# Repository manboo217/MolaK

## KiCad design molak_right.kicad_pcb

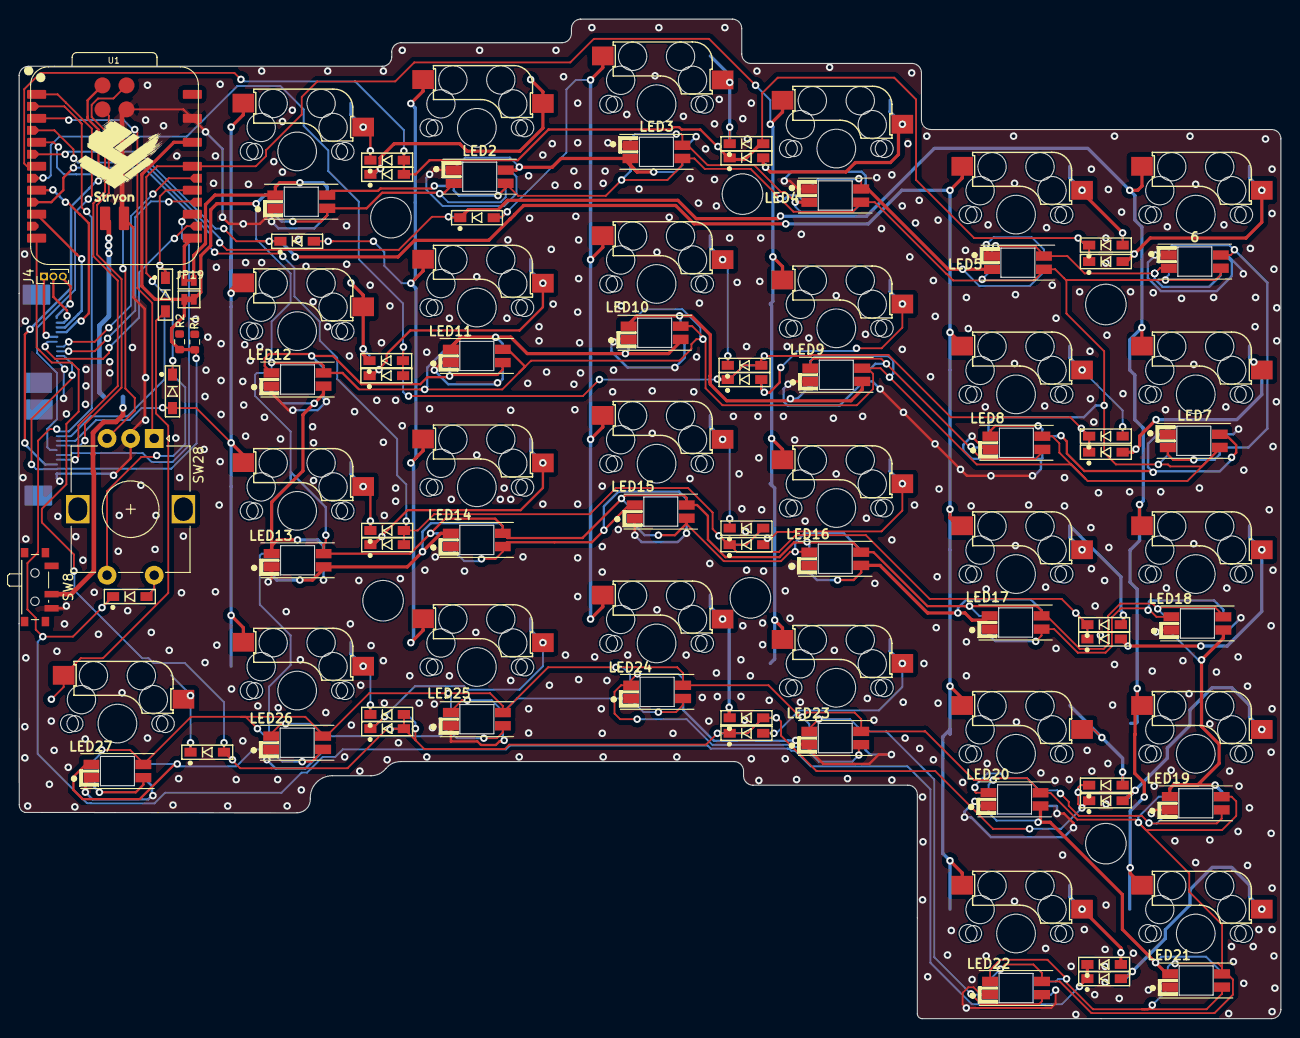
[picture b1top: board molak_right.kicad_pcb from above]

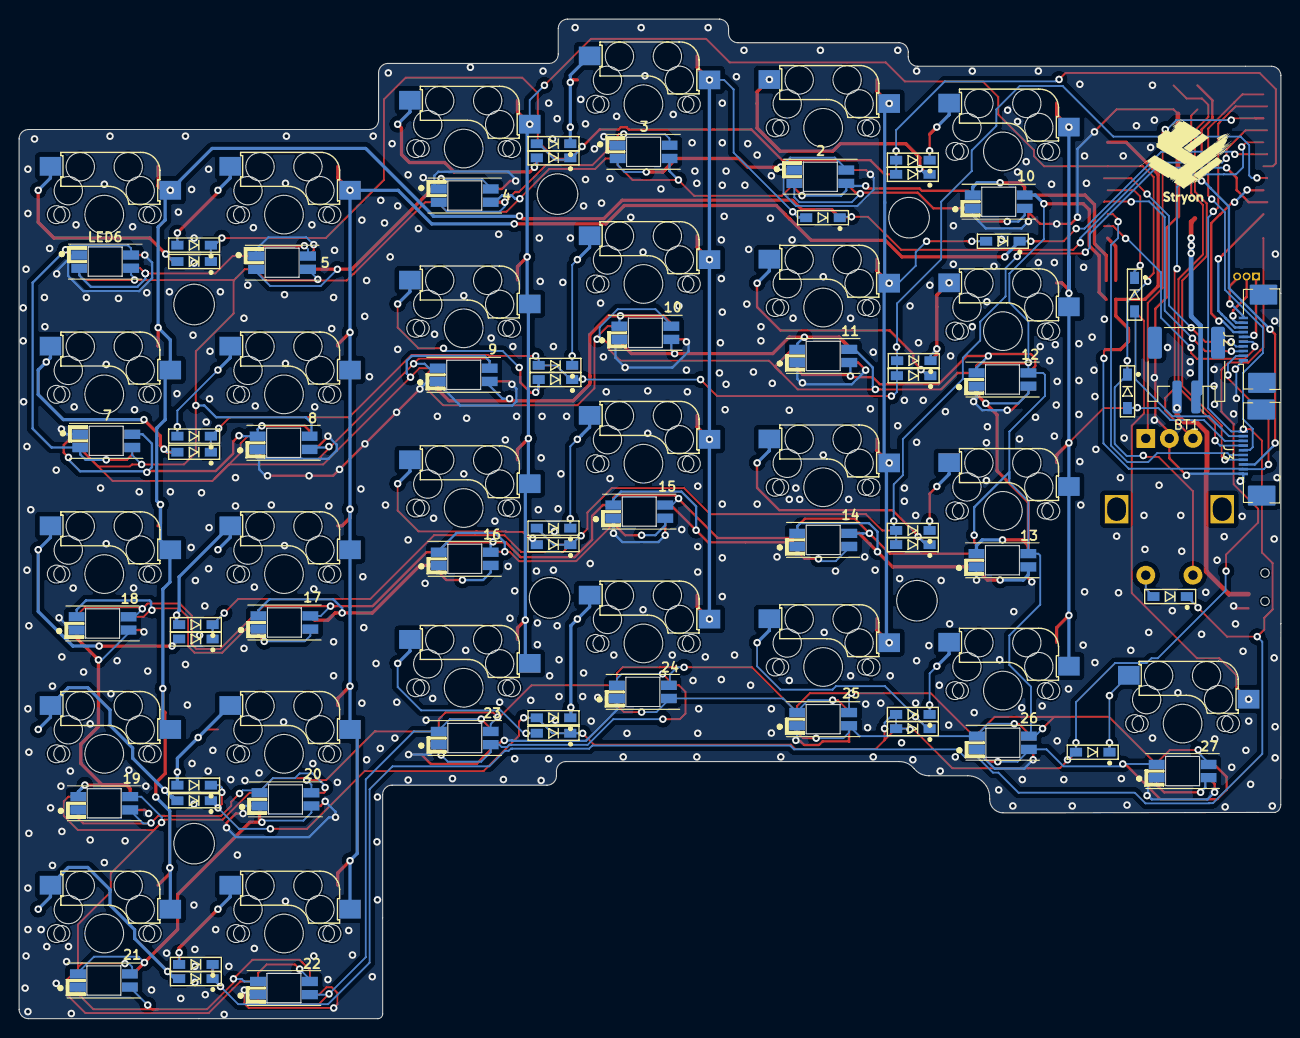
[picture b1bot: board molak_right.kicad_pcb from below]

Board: 2 copper layers, 133.7 x 105.9 mm, 103 parts (4 on the bottom side), 89 nets.

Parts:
BT1: BATT; JST_PH_S2B-PH-SM4-TB_1x02-1MP_P2.00mm_Horizontal
D1, D2, D3, D4, D5, D6, D7, D9, D11, D13, D15, D16, D17, D18, D19, D20, D21, D22, D23, D24, D25, D26, D27, D31, D32, D33, D34: D; D3_SMD_v2_BOTH
D8, D10, D12, D14, D28: D; D3_SMD_v2
J2, J3: Conn; Molex_54548-1071_1x10-1MP_P0.5mm_Horizontal
J4: Conn_01x03_Pin; PinHeader_1x03_P1.00mm_Vertical
J5, J6, J7, J9, J10, J12: Conn_01x01-Connector_Generic; MountingHole_4.3mm_M4
JP19: Device_Jumper_NO_Small; JP06
JP20: Device_Jumper_NO_Small; JP025
LED1: YS-SK6812MINI-E; LED_SK6812MINI_PLCC4_3.5x3.5mm_P1.75mm
LED2, LED3, LED4, LED5, LED6, LED7: YS-SK6812MINI-E; YS-SK6812MINI-Keyball-BL
LED8, LED9, LED10, LED11, LED12, LED13, LED14, LED15, LED16, LED17, LED18, LED19, LED20, LED21, LED22, LED23, LED24, LED25, LED26, LED27: YS-SK6812MINI-E; YS-SK6812MINI-Keyball-TL
R1, R2: PULL_UP; R_0603_1608Metric
SW1, SW2, SW3, SW4, SW5, SW6, SW7, SW9, SW10, SW11, SW12, SW13, SW14, SW15, SW16, SW17, SW18, SW19, SW20, SW21, SW22, SW23, SW24, SW25, SW26, SW27: SW_PUSH-kbd; CherryMX_MidHeight_Hotswap
SW8: SW_SPDT; SW_SPDT_PCM12
SW28: RotaryEncoder_Switch; RotaryEncoder_Alps_EC12E-Switch_Vertical_H20mm
U1: XIAO-nRF52840-Plus-SMD
e1: SW_PUSH-kbd; CherryMX_MidHeight_Hotswap

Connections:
Bat: BT1.1 (+), U1.32 (VBAT)
COL0: D31.1 (K), SW1.1, SW7.1, SW13.1, SW19.1, SW26.1, U1.16 (P0.19_I2S_SCK)
COL1: D32.1 (K), SW2.1, SW14.1, SW20.1, SW27.1, U1.17 (P1.01_I2S_WS), e1.1
COL2: D33.1 (K), SW3.1, SW9.1, SW15.1, SW21.1, SW28.S2, U1.11 (P1.15_MOSI_D10)
COL2_conn: D33.2 (A), J3.8, SW6.1, SW12.1, SW18.1, SW24.1
COL3: D34.1 (K), U1.10 (P1.14_MISO_D9)
COL3_conn: D34.2 (A), J3.9, SW25.1
ECA: SW28.A, U1.2 (P0.03_AIN1_LOW_A1_D1)
ECB: SW28.B, U1.3 (P0.28_AIN4_LOW_A2_D2)
GND: J2.1, J3.1, LED1.3 (GND), LED2.3 (GND), LED3.3 (GND), LED4.3 (GND), LED5.3 (GND), LED6.3 (GND), LED7.3 (GND), LED8.3 (GND), LED9.3 (GND), LED10.3 (GND), LED11.3 (GND), LED12.3 (GND), LED13.3 (GND), LED14.3 (GND), LED15.3 (GND), LED16.3 (GND), LED17.3 (GND), LED18.3 (GND), LED19.3 (GND), LED20.3 (GND), LED21.3 (GND), LED22.3 (GND), LED23.3 (GND), LED24.3 (GND), LED25.3 (GND), LED26.3 (GND), LED27.3 (GND), SW8.3 (C), SW28.C, U1.13 (GND), U1.27 (GND), U1.33 (GND)
LED: JP20.1, U1.8 (P1.12_RX_D7)
MISO: J2.4, U1.23 (P1.07_MOSI1)
MOSI: J2.3, U1.22 (P1.05_MISO1)
MOTION: J3.6, U1.1 (P0.02_AIN0_LOW_A0_D0)
unnamed: BT1.2 (-), SW8.2 (B)
unnamed: D1.2 (A), SW1.2
unnamed: D2.2 (A), SW2.2
unnamed: D3.2 (A), SW3.2
unnamed: D4.1 (K), SW4.2
unnamed: D5.1 (K), SW5.2
unnamed: D6.1 (K), SW6.2
unnamed: D7.2 (A), SW7.2
unnamed: D8.2 (A), e1.2
unnamed: D9.2 (A), SW9.2
unnamed: D10.1 (K), SW10.2
unnamed: D11.1 (K), SW11.2
unnamed: D12.1 (K), SW12.2
unnamed: D13.2 (A), SW13.2
unnamed: D14.2 (A), SW14.2
unnamed: D15.2 (A), SW15.2
unnamed: D16.1 (K), SW16.2
unnamed: D17.1 (K), SW17.2
unnamed: D18.1 (K), SW18.2
unnamed: D19.2 (A), SW19.2
unnamed: D20.2 (A), SW20.2
unnamed: D21.2 (A), SW21.2
unnamed: D22.1 (K), SW22.2
unnamed: D23.1 (K), SW23.2
unnamed: D24.1 (K), SW24.2
unnamed: D25.1 (K), SW25.2
unnamed: D26.2 (A), SW26.2
unnamed: D27.2 (A), SW27.2
unnamed: D31.2 (A), SW4.1, SW10.1, SW16.1, SW22.1
unnamed: D32.2 (A), SW5.1, SW11.1, SW17.1, SW23.1
unnamed: JP20.2, LED1.4 (DIN)
unnamed: LED1.2 (DOUT), LED2.4 (DIN)
unnamed: JP19.1, LED1.1 (VDD), LED2.1 (VDD), LED3.1 (VDD), LED4.1 (VDD), LED5.1 (VDD), LED6.1 (VDD), LED7.1 (VDD), LED8.1 (VDD), LED9.1 (VDD), LED10.1 (VDD), LED11.1 (VDD), LED12.1 (VDD), LED13.1 (VDD), LED14.1 (VDD), LED15.1 (VDD), LED16.1 (VDD), LED17.1 (VDD), LED18.1 (VDD), LED19.1 (VDD), LED20.1 (VDD), LED21.1 (VDD), LED22.1 (VDD), LED23.1 (VDD), LED24.1 (VDD), LED25.1 (VDD), LED26.1 (VDD), LED27.1 (VDD)
unnamed: LED2.2 (DOUT), LED3.4 (DIN)
unnamed: LED3.2 (DOUT), LED4.4 (DIN)
unnamed: LED4.2 (DOUT), LED5.4 (DIN)
unnamed: LED5.2 (DOUT), LED6.4 (DIN)
unnamed: LED6.2 (DOUT), LED7.4 (DIN)
unnamed: LED7.2 (DOUT), LED8.4 (DIN)
unnamed: LED8.2 (DOUT), LED9.4 (DIN)
unnamed: LED9.2 (DOUT), LED10.4 (DIN)
unnamed: LED10.2 (DOUT), LED11.4 (DIN)
unnamed: LED11.2 (DOUT), LED12.4 (DIN)
unnamed: LED12.2 (DOUT), LED13.4 (DIN)
unnamed: LED13.2 (DOUT), LED14.4 (DIN)
unnamed: LED14.2 (DOUT), LED15.4 (DIN)
unnamed: LED15.2 (DOUT), LED16.4 (DIN)
unnamed: LED16.2 (DOUT), LED17.4 (DIN)
unnamed: LED17.2 (DOUT), LED18.4 (DIN)
unnamed: LED18.2 (DOUT), LED19.4 (DIN)
unnamed: LED19.2 (DOUT), LED20.4 (DIN)
unnamed: LED20.2 (DOUT), LED21.4 (DIN)
unnamed: LED21.2 (DOUT), LED22.4 (DIN)
unnamed: LED22.2 (DOUT), LED23.4 (DIN)
unnamed: LED23.2 (DOUT), LED24.4 (DIN)
unnamed: LED24.2 (DOUT), LED25.4 (DIN)
unnamed: LED25.2 (DOUT), LED26.4 (DIN)
unnamed: LED26.2 (DOUT), LED27.4 (DIN)
RESET: J3.7, U1.26 (REST)
ROW0: D1.1 (K), D2.1 (K), D3.1 (K), D4.2 (A), D5.2 (A), D6.2 (A), U1.4 (P0.29_AIN5_LOW_A3_D3)
ROW1: D7.1 (K), D8.1 (K), D9.1 (K), D10.2 (A), D11.2 (A), D12.2 (A), U1.18 (P0.09/NFC1/RX1)
ROW2: D13.1 (K), D14.1 (K), D15.1 (K), D16.2 (A), D17.2 (A), D18.2 (A), U1.19 (P0.10/NFC2/TX1)
ROW3: D19.1 (K), D20.1 (K), D21.1 (K), D22.2 (A), D23.2 (A), D24.2 (A), D25.2 (A), U1.7 (P1.11_TX_D6)
ROW4: D26.1 (K), D27.1 (K), D28.1 (K), J3.10, U1.15 (P0.15_I2S_SD)
S1: D28.2 (A), SW28.S1
SCL: J2.8, R2.2, U1.6 (P0.05_AIN3_A5_D5)
SCLK: J3.4, U1.25 (SWDCLK)
SCLK2: J2.5, U1.21 (P1.03_SCK1)
SDA: J2.7, R1.2, U1.5 (P0.04_AIN2_A4_D4)
SDIO: J3.3, U1.24 (SWDIO)
VCC: J2.2, J3.2, JP19.2, R1.1, R2.1, U1.12 (3V3)
nCS: J3.5, U1.9 (P1.13_SCK_D8)
nCS2: J2.6, J4.1
nCS3: J2.9, J4.2
nCS4: J2.10, J4.3

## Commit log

2025-10-07 first commit for keyball61 right
2025-11-15 Molak: Update v0.1
